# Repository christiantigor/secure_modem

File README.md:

secure_modem
============

Secure modem

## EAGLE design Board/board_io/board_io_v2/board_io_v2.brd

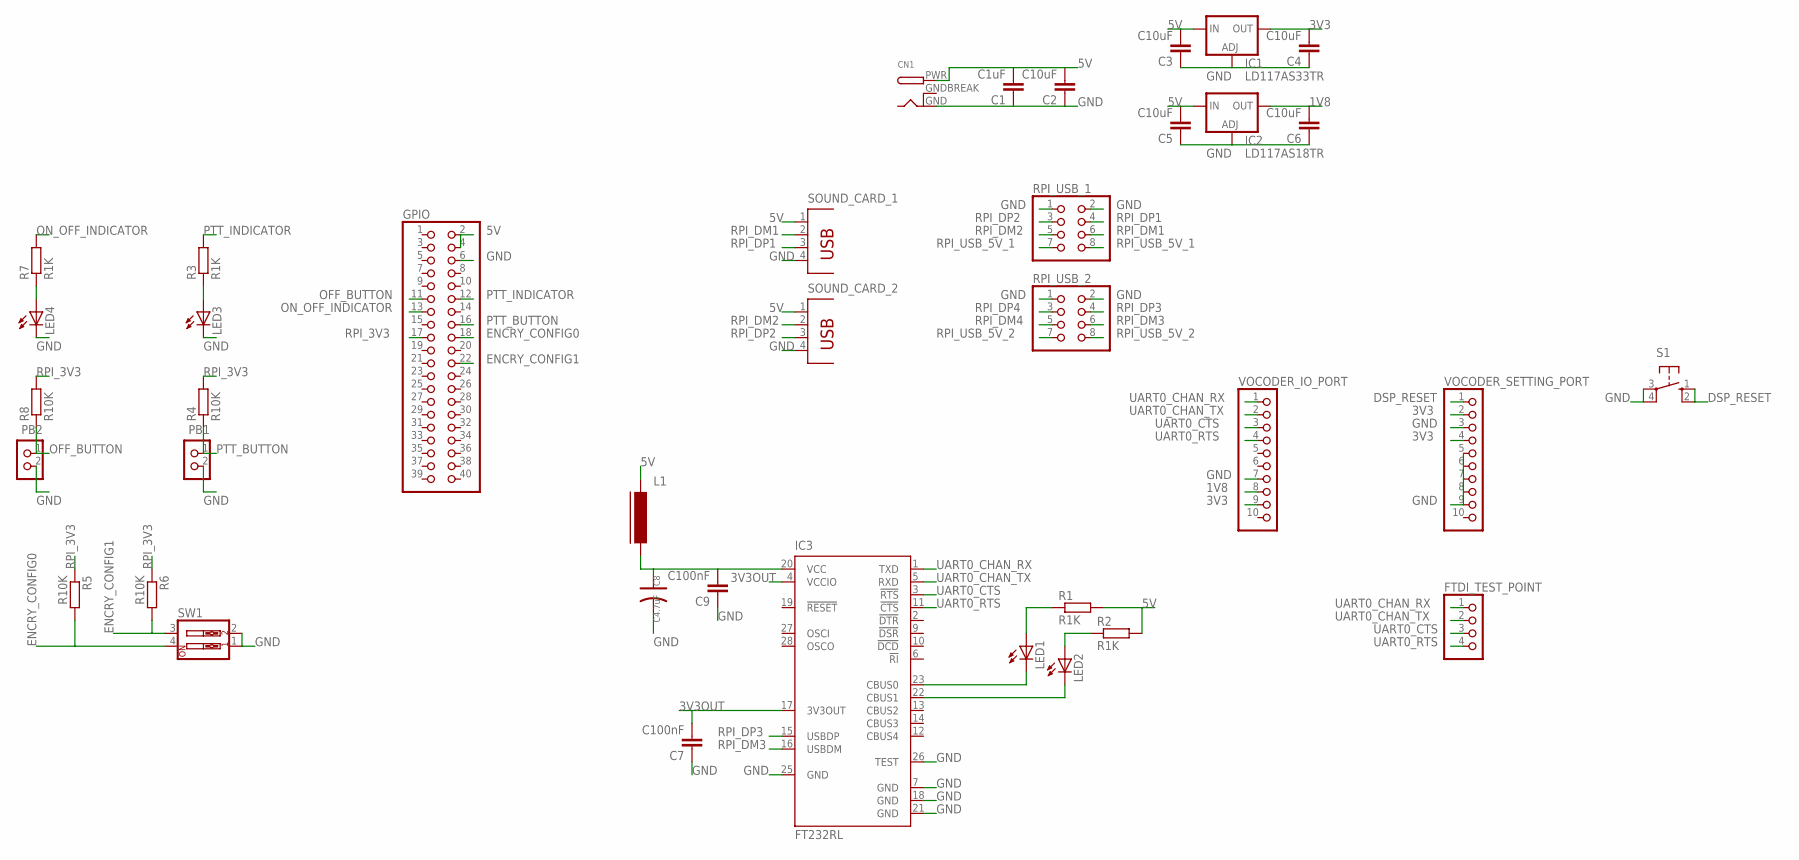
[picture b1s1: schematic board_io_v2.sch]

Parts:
C1: C1uF; C0805
C2, C3, C4, C5, C6: C10uF; C0805
C7, C9: C100nF; C0805
C8: C4.7uF; AVX-C
CN1: DCBARRELPTH; DCJACK_2MM_PTH
FTDI_TEST_POINT: PINHD-1X4; 1X04
GPIO: PINHD-2X20; 2X20
IC1: LD117AS33TR; SOT223
IC2: LD117AS18TR; SOT223
IC3: FT232RL; SSOP28
L1: FERRITE-0603; FB603
LED1, LED2, LED3, LED4: LEDCHIP-LED0805; CHIP-LED0805
PB1, PB2: CON_HEADER_1X02-PTH; M1X2
R1, R2, R3, R7: R1K; R0805
R4, R5, R6, R8: R10K; R0805
RPI_USB_1, RPI_USB_2: PINHD-2X4; 2X04
S1: 10-XX; B3F-10XX
SOUND_CARD_1, SOUND_CARD_2: PN87520
SW1: SW_DIP-2; DIPSWITCH-02
VOCODER_IO_PORT: PINHD-1X10; 1X10
VOCODER_SETTING_PORT: PINHD-1X10; 1X10

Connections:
1V8: C6.2, IC2.4 (OUT), VOCODER_IO_PORT.8
3V3: C4.2, IC1.4 (OUT), VOCODER_IO_PORT.9, VOCODER_SETTING_PORT.2, VOCODER_SETTING_PORT.4
3V3OUT: C7.2, IC3.4 (VCCIO), IC3.17 (3V3OUT)
5V: C1.2, C2.2, C3.2, C5.2, CN1.PWR, GPIO.2, GPIO.4, IC1.3 (IN), IC2.3 (IN), L1.1, R1.2, R2.2, SOUND_CARD_1.1, SOUND_CARD_2.1
DSP_RESET: S1.1 (S), S1.2 (S1), VOCODER_SETTING_PORT.1
ENCRY_CONFIG0: GPIO.18, R5.2, SW1.4
ENCRY_CONFIG1: GPIO.22, R6.2, SW1.3
GND: C1.1, C2.1, C3.1, C4.1, C5.1, C6.1, C7.1, C8.- (2), C9.1, CN1.GND, GPIO.6, IC1.1 (ADJ), IC2.1 (ADJ), IC3.7 (GND), IC3.18 (GND), IC3.21 (GND), IC3.25 (GND), IC3.26 (TEST), LED3.C, LED4.C, PB1.2, PB2.2, RPI_USB_1.1, RPI_USB_1.2, RPI_USB_2.1, RPI_USB_2.2, S1.3, S1.4 (P1), SOUND_CARD_1.4, SOUND_CARD_2.4, SW1.1, SW1.2, VOCODER_IO_PORT.7, VOCODER_SETTING_PORT.3, VOCODER_SETTING_PORT.5, VOCODER_SETTING_PORT.6, VOCODER_SETTING_PORT.7, VOCODER_SETTING_PORT.8, VOCODER_SETTING_PORT.9
GNDBREAK: CN1.GNDBREAK
unnamed: C8.+ (1), C9.2, IC3.20 (VCC), L1.2
unnamed: IC3.22 (CBUS1), LED2.C
unnamed: IC3.23 (CBUS0), LED1.C
unnamed: LED2.A, R2.1
unnamed: LED1.A, R1.1
unnamed: LED4.A, R7.1
unnamed: LED3.A, R3.1
OFF_BUTTON: GPIO.11, PB2.1, R8.1
ON_OFF_INDICATOR: GPIO.13, R7.2
PTT_BUTTON: GPIO.16, PB1.1, R4.1
PTT_INDICATOR: GPIO.12, R3.2
RPI_3V3: GPIO.17, R4.2, R5.1, R6.1, R8.2
RPI_DM1: RPI_USB_1.6, SOUND_CARD_1.2
RPI_DM2: RPI_USB_1.5, SOUND_CARD_2.2
RPI_DM3: IC3.16 (USBDM), RPI_USB_2.6
RPI_DM4: RPI_USB_2.5
RPI_DP1: RPI_USB_1.4, SOUND_CARD_1.3
RPI_DP2: RPI_USB_1.3, SOUND_CARD_2.3
RPI_DP3: IC3.15 (USBDP), RPI_USB_2.4
RPI_DP4: RPI_USB_2.3
RPI_USB_5V_1: RPI_USB_1.7, RPI_USB_1.8
RPI_USB_5V_2: RPI_USB_2.7, RPI_USB_2.8
UART0_CHAN_RX: FTDI_TEST_POINT.1, IC3.1 (TXD), VOCODER_IO_PORT.1
UART0_CHAN_TX: FTDI_TEST_POINT.2, IC3.5 (RXD), VOCODER_IO_PORT.2
UART0_CTS: FTDI_TEST_POINT.3, IC3.3 (!RTS), VOCODER_IO_PORT.3
UART0_RTS: FTDI_TEST_POINT.4, IC3.11 (!CTS), VOCODER_IO_PORT.4

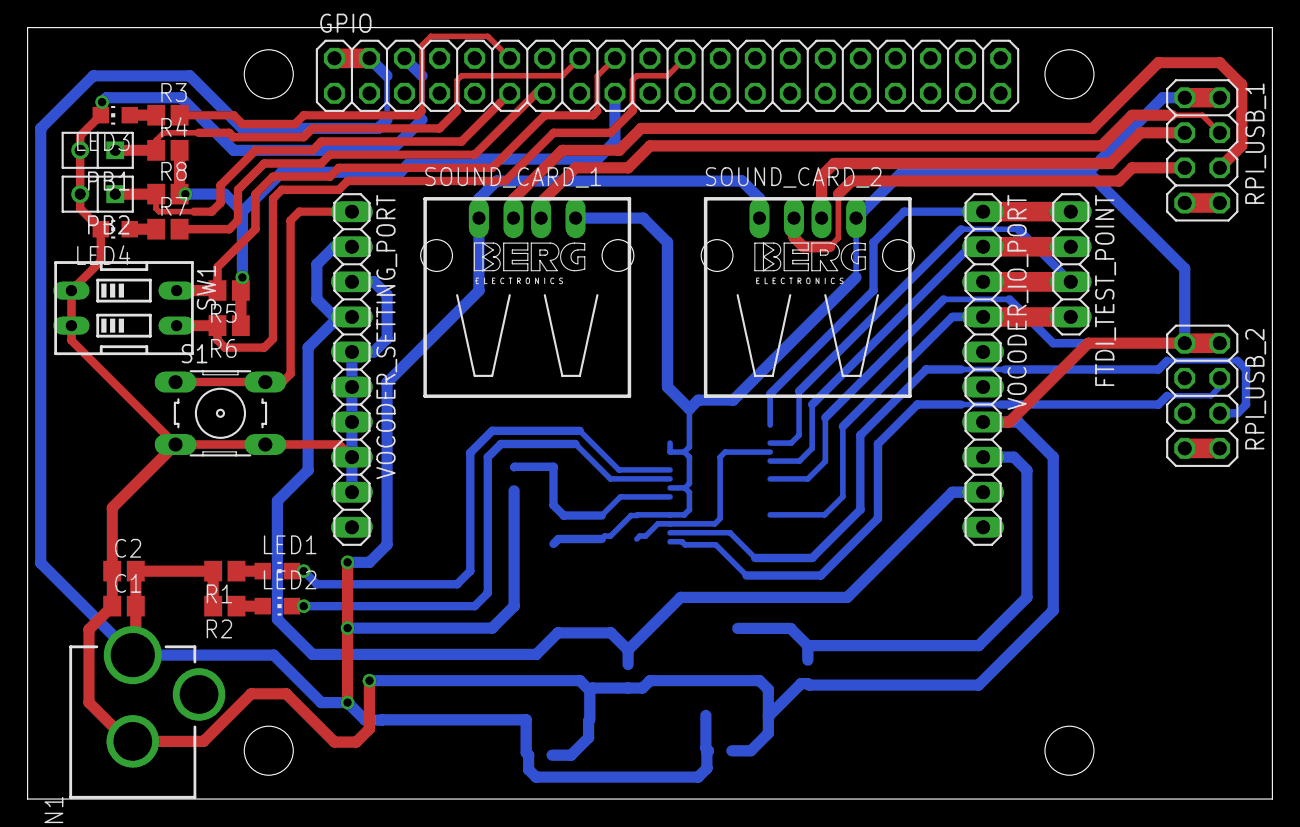
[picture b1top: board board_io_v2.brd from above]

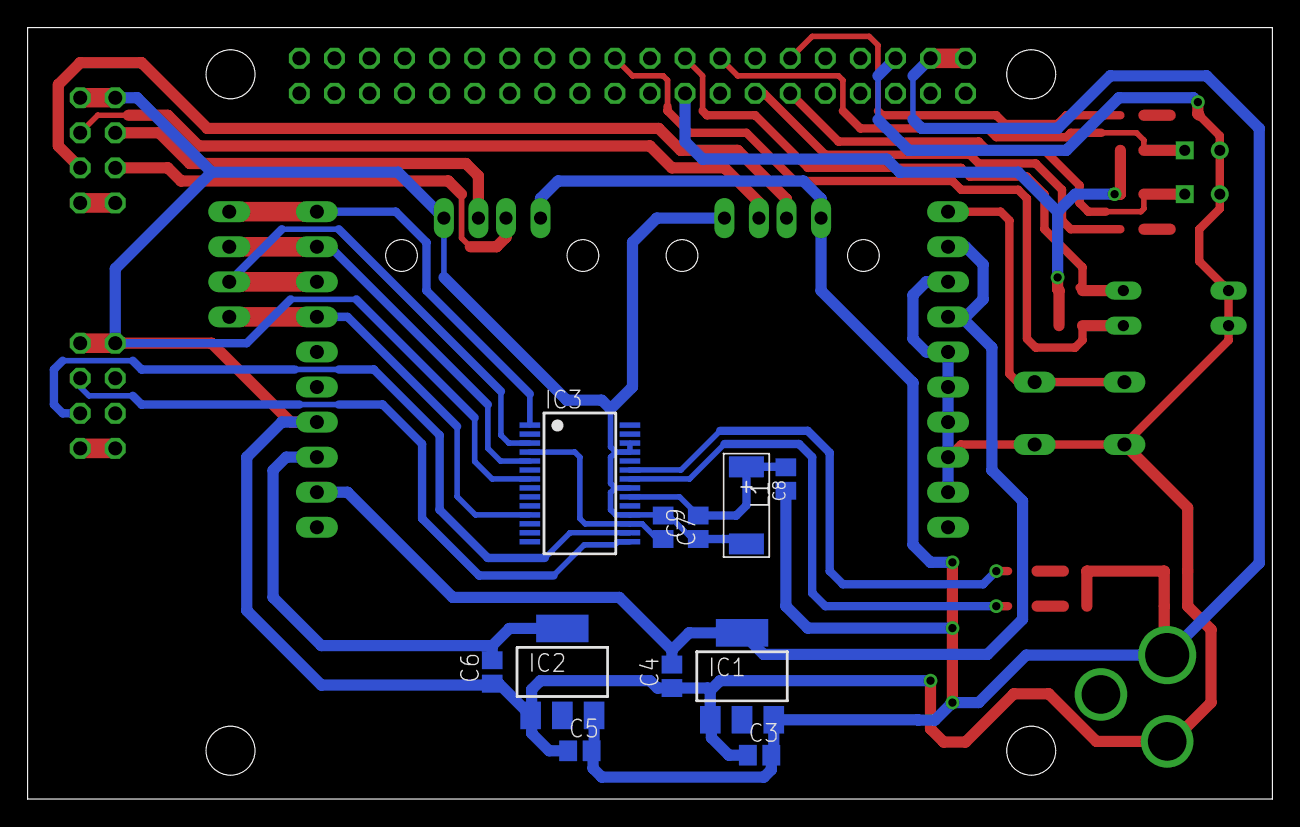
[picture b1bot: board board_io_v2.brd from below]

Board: 2 copper layers, 90.2 x 55.9 mm, 38 parts (11 on the bottom side), 32 nets.

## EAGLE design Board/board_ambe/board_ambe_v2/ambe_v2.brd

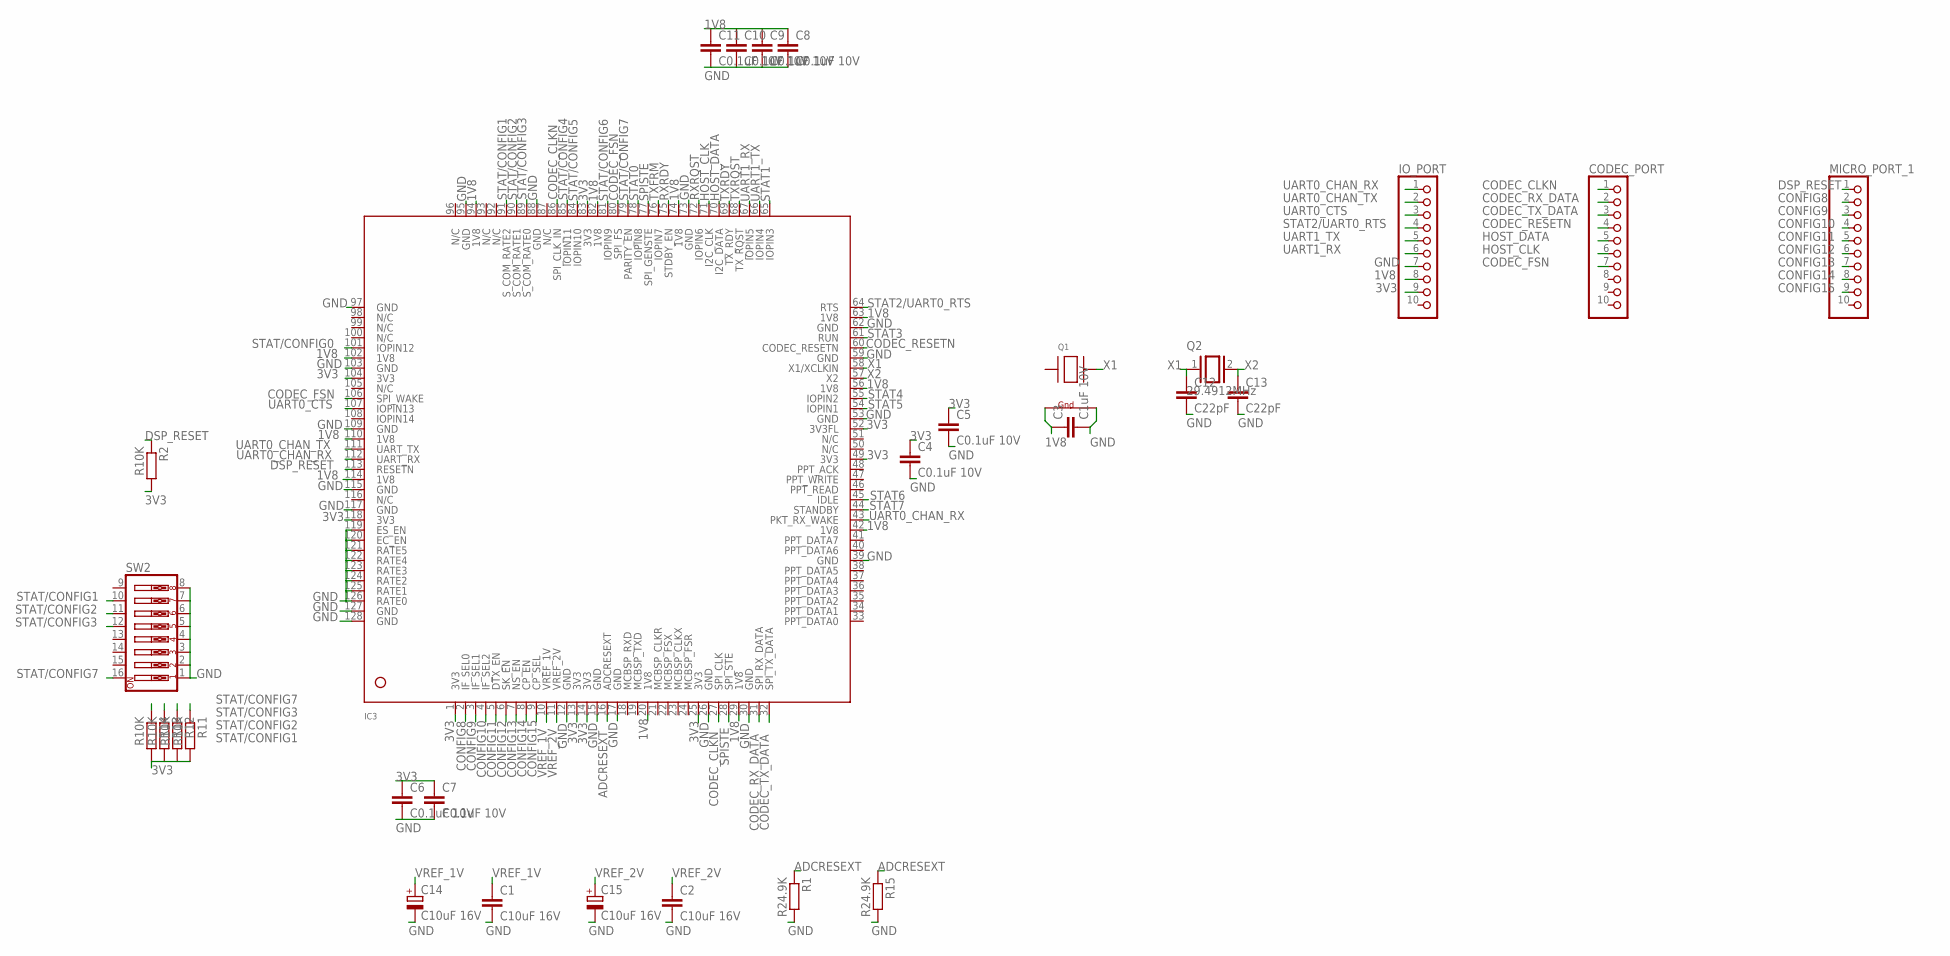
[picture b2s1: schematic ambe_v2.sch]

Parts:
C1, C2: C10uF 16V; C0805
C3: C1uF 10V; C0805
C4, C5, C6, C7, C8, C9, C10, C11: C0.1uF 10V; C0805
C12, C13: C22pF; C025-024X044
C14, C15: C10uF 16V; E2-4
CODEC_PORT: PINHD-1X10; 1X10
IC3: AMBE-3000LQFP-128; LQFP-128
IO_PORT: PINHD-1X10; 1X10
MICRO_PORT_1: PINHD-1X10; 1X10
Q1: XTAL-4-3225; NX3225
Q2: 29.4912MHz; QS
R1: R24.9K; R0805
R2, R11, R12, R13, R14: R10K; R0805
R15: R24.9K; 0207/2V
SW2: SW_DIP-8; DIPSWITCH-08

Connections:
1V8: C3.1, C8.1, C9.1, C10.1, C11.1, IC3.20 (1V8), IC3.29 (1V8), IC3.42 (1V8), IC3.56 (1V8), IC3.63 (1V8), IC3.74 (1V8), IC3.82 (1V8), IC3.94 (1V8), IC3.102 (1V8), IC3.110 (1V8), IC3.114 (1V8), IO_PORT.8, Q1.4 (G1)
3V3: C4.1, C5.1, C6.1, C7.1, IC3.1 (3V3), IC3.13 (3V3), IC3.14 (3V3), IC3.25 (3V3), IC3.49 (3V3), IC3.52 (3V3FL), IC3.83 (3V3), IC3.104 (3V3), IC3.118 (3V3), IO_PORT.9, R2.2, R11.2, R12.2, R13.2, R14.2
ADCRESEXT: IC3.16 (ADCRESEXT), R1.1, R15.1
CODEC_CLKN: CODEC_PORT.1, IC3.27 (SPI_CLK), IC3.86 (SPI_CLK_IN)
CODEC_FSN: CODEC_PORT.7, IC3.80 (SPI_FS), IC3.106 (SPI_WAKE)
CODEC_RESETN: CODEC_PORT.4, IC3.60 (CODEC_RESETN)
CODEC_RX_DATA: CODEC_PORT.2, IC3.31 (SPI_RX_DATA)
CODEC_TX_DATA: CODEC_PORT.3, IC3.32 (SPI_TX_DATA)
CONFIG8: IC3.2 (IF_SEL0), MICRO_PORT_1.2
CONFIG9: IC3.3 (IF_SEL1), MICRO_PORT_1.3
CONFIG10: IC3.4 (IF_SEL2), MICRO_PORT_1.4
CONFIG11: IC3.5 (DTX_EN), MICRO_PORT_1.5
CONFIG12: IC3.6 (SK_EN), MICRO_PORT_1.6
CONFIG13: IC3.7 (NS_EN), MICRO_PORT_1.7
CONFIG14: IC3.8 (CP_EN), MICRO_PORT_1.8
CONFIG15: IC3.9 (CP_SEL), MICRO_PORT_1.9
DSP_RESET: IC3.113 (RESETN), MICRO_PORT_1.1, R2.1
GND: C1.2, C2.2, C3.2, C4.2, C5.2, C6.2, C7.2, C8.2, C9.2, C10.2, C11.2, C12.2, C13.2, C14.-, C15.-, IC3.12 (GND), IC3.15 (GND), IC3.17 (GND), IC3.26 (GND), IC3.30 (GND), IC3.39 (GND), IC3.53 (GND), IC3.59 (GND), IC3.62 (GND), IC3.73 (GND), IC3.88 (GND), IC3.95 (GND), IC3.97 (GND), IC3.103 (GND), IC3.109 (GND), IC3.115 (GND), IC3.117 (GND), IC3.119 (ES_EN), IC3.120 (EC_EN), IC3.121 (RATE5), IC3.122 (RATE4), IC3.123 (RATE3), IC3.124 (RATE2), IC3.125 (RATE1), IC3.126 (RATE0), IC3.127 (GND), IC3.128 (GND), IO_PORT.7, Q1.2 (G2), R1.2, R15.2, SW2.1, SW2.2, SW2.3, SW2.4, SW2.5, SW2.6, SW2.7, SW2.8
HOST_CLK: CODEC_PORT.6, IC3.71 (I2C_CLK)
HOST_DATA: CODEC_PORT.5, IC3.70 (I2C_DATA)
RXRDY: IC3.75 (STDBY_EN)
RXRQST: IC3.72 (IOPIN6)
SPISTE: IC3.28 (SPI_STE), IC3.77 (SPI_GENSTE)
STAT0: IC3.78 (IOPIN8)
STAT1: IC3.65 (IOPIN3)
STAT2/UART0_RTS: IC3.64 (RTS), IO_PORT.4
STAT3: IC3.61 (RUN)
STAT4: IC3.55 (IOPIN2)
STAT5: IC3.54 (IOPIN1)
STAT6: IC3.45 (IDLE)
STAT7: IC3.44 (STANDBY)
STAT/CONFIG0: IC3.101 (IOPIN12)
STAT/CONFIG1: IC3.91 (S_COM_RATE2), R14.1, SW2.10
STAT/CONFIG2: IC3.90 (S_COM_RATE1), R13.1, SW2.11
STAT/CONFIG3: IC3.89 (S_COM_RATE0), R12.1, SW2.12
STAT/CONFIG4: IC3.85 (IOPIN11)
STAT/CONFIG5: IC3.84 (IOPIN10)
STAT/CONFIG6: IC3.81 (IOPIN9)
STAT/CONFIG7: IC3.79 (PARITY_EN), R11.1, SW2.16
TXFRM: IC3.76 (IOPIN7)
TXRDY: IC3.69 (TX_RDY)
TXRQST: IC3.68 (TX_RQST)
UART0_CHAN_RX: IC3.43 (PKT_RX_WAKE), IC3.112 (UART_RX), IO_PORT.1
UART0_CHAN_TX: IC3.111 (UART_TX), IO_PORT.2
UART0_CTS: IC3.107 (IOPIN13), IO_PORT.3
UART1_RX: IC3.67 (IOPIN5), IO_PORT.6
UART1_TX: IC3.66 (IOPIN4), IO_PORT.5
VREF_1V: C1.1, C14.+, IC3.10 (VREF_1V)
VREF_2V: C2.1, C15.+, IC3.11 (VREF_2V)
X1: C12.1, IC3.58 (X1/XCLKIN), Q1.3 (X2), Q2.1
X2: C13.1, IC3.57 (X2), Q2.2

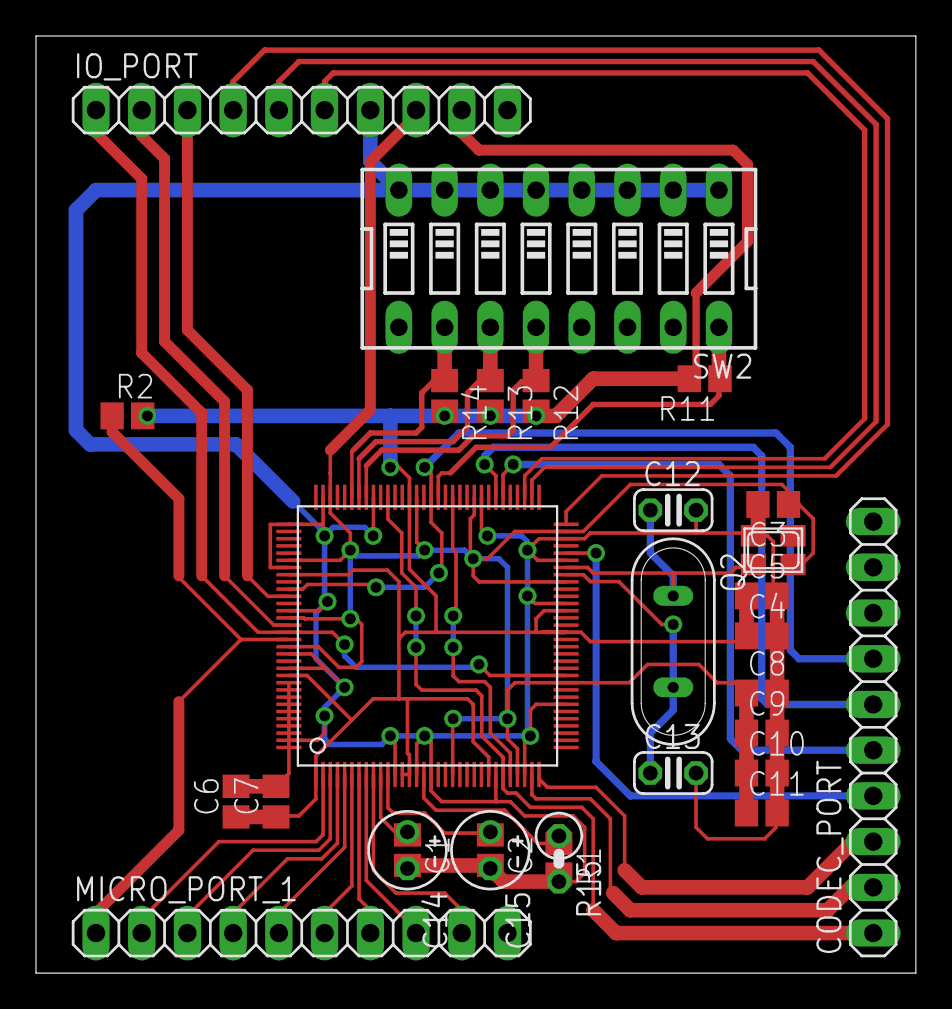
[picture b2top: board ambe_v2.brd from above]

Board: 2 copper layers, 48.9 x 52.1 mm, 29 parts (0 on the bottom side), 35 nets.

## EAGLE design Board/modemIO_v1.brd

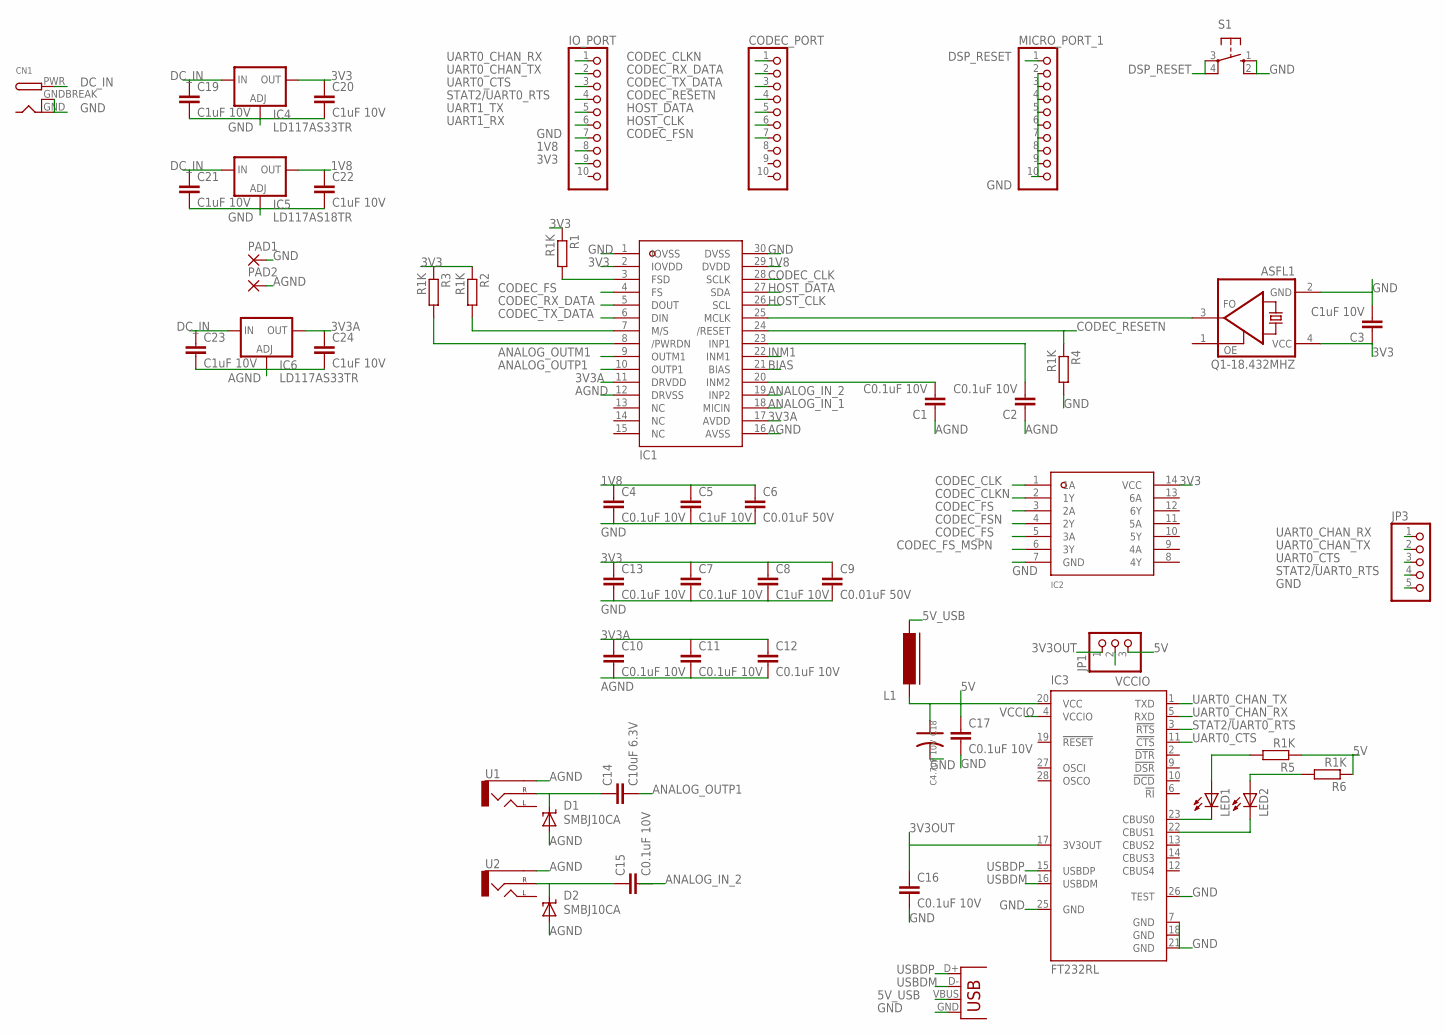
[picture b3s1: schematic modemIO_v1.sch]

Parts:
C1, C2, C4, C7, C10, C11, C12, C13, C15, C16, C17: C0.1uF 10V; C0805
C3, C5, C8, C19, C20, C21, C22, C23, C24: C1uF 10V; C0805
C6, C9: C0.01uF 50V; C0805
C14: C10uF 6.3V; C0805
C18: C4.7uF 10V; AVX-C
CN1: DCBARRELPTH; DCJACK_2MM_PTH
CODEC_PORT: PINHD-1X10; 1X10
D1, D2: SMBJ10CA; SMBJ
IC1: TLV320AIC14R-PDSO-G30; R-PDSO-G30
IC2: SN74LVC04ADRR-PDSO-G14; R-PDSO-G14
IC3: FT232RL; SSOP28
IC4, IC6: LD117AS33TR; SOT223
IC5: LD117AS18TR; SOT223
IO_PORT: PINHD-1X10; 1X10
JP1: PINHD-1X3; 1X03
JP2: USBSMD; USB-MINIB
JP3: PINHD-1X5; 1X05
L1: FERRITE-0603; FB603
LED1, LED2: LEDCHIP-LED0805; CHIP-LED0805
MICRO_PORT_1: PINHD-1X10; 1X10
PAD1, PAD2: SMD2; SMD1,27-2,54
Q1-18.432MHZ: ASFL1; ASF
R1, R2, R3, R4, R5, R6: R1K; R0805
S1: 10-XX; B3F-10XX
U1, U2: AUDIO-JACKSMD2; AUDIO-JACK-3.5MM-SMD

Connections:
1V8: C4.1, C5.1, C6.1, C22.1, IC1.29 (DVDD), IC5.4 (OUT), IO_PORT.8
3V3: C3.1, C7.1, C8.1, C9.1, C13.1, C20.1, IC1.2 (IOVDD), IC2.14 (VCC), IC4.4 (OUT), IO_PORT.9, Q1-18.432MHZ.4 (VCC), R1.1, R2.1, R3.1
3V3A: C10.1, C11.1, C12.1, C24.1, IC1.11 (DRVDD), IC1.17 (AVDD), IC6.4 (OUT)
3V3OUT: C16.1, IC3.17 (3V3OUT), JP1.1
5V: C17.1, C18.+ (1), IC3.20 (VCC), JP1.3, L1.1, R5.1, R6.1
5V_USB: JP2.VBUS, L1.2
AGND: C1.1, C2.1, C10.2, C11.2, C12.2, C23.2, C24.2, D1.A, D2.A, IC1.12 (DRVSS), IC1.16 (AVSS), IC6.1 (ADJ), PAD2.1, U1.SLEEVE, U2.SLEEVE
ANALOG_IN_1: IC1.18 (MICIN)
ANALOG_IN_2: C15.2, IC1.19 (INP2)
ANALOG_OUTM1: IC1.9 (OUTM1)
ANALOG_OUTP1: C14.2, IC1.10 (OUTP1)
BIAS: IC1.21 (BIAS)
CODEC_CLK: IC1.28 (SCLK), IC2.1 (1A)
CODEC_CLKN: CODEC_PORT.1, IC2.2 (1Y)
CODEC_FS: IC1.4 (FS), IC2.3 (2A), IC2.5 (3A)
CODEC_FSN: CODEC_PORT.7, IC2.4 (2Y)
CODEC_FS_MSPN: IC2.6 (3Y)
CODEC_RESETN: CODEC_PORT.4, IC1.24 (/RESET), R4.1
CODEC_RX_DATA: CODEC_PORT.2, IC1.5 (DOUT)
CODEC_TX_DATA: CODEC_PORT.3, IC1.6 (DIN)
DC_IN: C19.1, C21.1, C23.1, CN1.PWR, IC4.3 (IN), IC5.3 (IN), IC6.3 (IN)
DSP_RESET: MICRO_PORT_1.1, S1.3, S1.4 (P1)
GND: C3.2, C4.2, C5.2, C6.2, C7.2, C8.2, C9.2, C13.2, C16.2, C17.2, C18.- (2), C19.2, C20.2, C21.2, C22.2, CN1.GND, CN1.GNDBREAK, IC1.1 (IOVSS), IC1.30 (DVSS), IC2.7 (GND), IC3.7 (GND), IC3.18 (GND), IC3.21 (GND), IC3.25 (GND), IC3.26 (TEST), IC4.1 (ADJ), IC5.1 (ADJ), IO_PORT.7, JP2.GND, JP3.5, MICRO_PORT_1.2, MICRO_PORT_1.3, MICRO_PORT_1.4, MICRO_PORT_1.5, MICRO_PORT_1.6, MICRO_PORT_1.7, MICRO_PORT_1.8, MICRO_PORT_1.9, MICRO_PORT_1.10, PAD1.1, Q1-18.432MHZ.2 (GND), R4.2, S1.1 (S), S1.2 (S1)
HOST_CLK: CODEC_PORT.6, IC1.26 (SCL)
HOST_DATA: CODEC_PORT.5, IC1.27 (SDA)
INM1: IC1.22 (INM1)
unnamed: C14.1, D1.C, U1.RING (RIGHT)
unnamed: IC3.23 (CBUS0), LED1.C
unnamed: IC1.3 (FSD), R1.2
unnamed: IC3.22 (CBUS1), LED2.C
unnamed: C15.1, D2.C, U2.RING (RIGHT)
unnamed: LED1.A, R5.2
unnamed: IC1.7 (M/S), R2.2
unnamed: IC1.8 (/PWRDN), R3.2
unnamed: LED2.A, R6.2
unnamed: C1.2, IC1.20 (INM2)
unnamed: C2.2, IC1.23 (INP1)
unnamed: IC1.25 (MCLK), Q1-18.432MHZ.3 (FO)
STAT2/UART0_RTS: IC3.3 (!RTS), IO_PORT.4, JP3.4
UART0_CHAN_RX: IC3.5 (RXD), IO_PORT.1, JP3.1
UART0_CHAN_TX: IC3.1 (TXD), IO_PORT.2, JP3.2
UART0_CTS: IC3.11 (!CTS), IO_PORT.3, JP3.3
UART1_RX: IO_PORT.6
UART1_TX: IO_PORT.5
USBDM: IC3.16 (USBDM), JP2.D-
USBDP: IC3.15 (USBDP), JP2.D+
VCCIO: IC3.4 (VCCIO), JP1.2

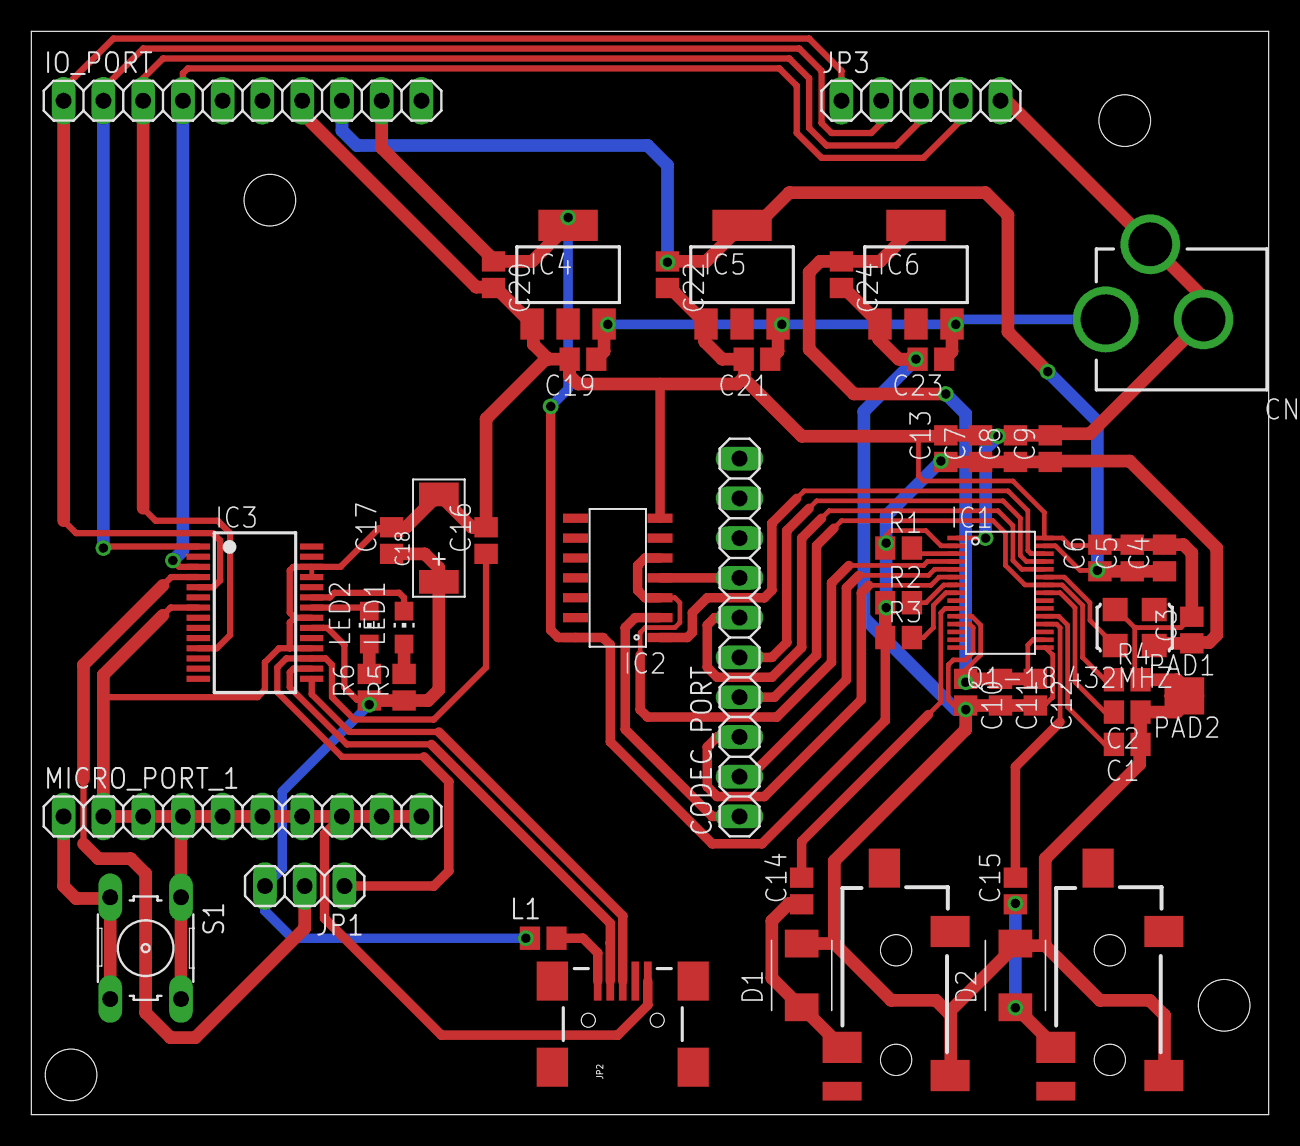
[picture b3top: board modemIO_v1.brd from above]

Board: 2 copper layers, 79.0 x 69.2 mm, 54 parts (0 on the bottom side), 40 nets.

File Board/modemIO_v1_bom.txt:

Partlist exported from C:/Users/tritronik/Documents/GitHub/secure_modem/Board/modemIO_v1.sch at 27/08/2014 12:49:14

Assembly variant: 

Qty Value                  Device                 Parts                                            
1                          10-XX                  S1                                               
2                          AUDIO-JACKSMD2         U1, U2                                           
1                          DCBARRELPTH            CN1                                              
1                          FERRITE-0603           L1                                               
2                          LEDCHIP-LED0805        LED1, LED2                                       
1                          PINHD-1X3              JP1                                              
1                          PINHD-1X5              JP3                                              
3                          PINHD-1X10             CODEC_PORT, IO_PORT, MICRO_PORT_1                
2                          SMD2                   PAD1, PAD2                                       
1   ASFL1                  ASFL1                  Q1-18.432MHZ                                     
11  C0.1uF 10V             C-EUC0805              C1, C2, C4, C7, C10, C11, C12, C13, C15, C16, C17
2   C0.01uF 50V            C-EUC0805              C6, C9                                           
9   C1uF 10V               C-EUC0805              C3, C5, C8, C19, C20, C21, C22, C23, C24         
1   C4.7uF 10V             C-POLAR-C              C18                                              
1   C10uF 6.3V             C-EUC0805              C14                                              
1   FT232RL                FT232RL                IC3                                              
1   LD117AS18TR            LD117AS18TR            IC5                                              
2   LD117AS33TR            LD117AS33TR            IC4, IC6                                         
6   R1K                    R-EU_R0805             R1, R2, R3, R4, R5, R6                           
2   SMBJ10CA               SUPPRESSOR-SMBJ        D1, D2                                           
1   SN74LVC04ADRR-PDSO-G14 SN74LVC04ADRR-PDSO-G14 IC2                                              
1   TLV320AIC14R-PDSO-G30  TLV320AIC14R-PDSO-G30  IC1                                              
1   USBSMD                 USBSMD                 JP2

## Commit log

2014-07-22 :space_invader: Added .gitattributes & .gitignore files
2014-07-25 Second commit
2014-07-25 Add DV3000DS and custom lib
2014-08-04 Progress on routing board
2014-08-05 Finish routing ambe board
2014-08-05 Create modemIO
2014-08-05 Add custom lib for codec and inverter
2014-08-07 + pull up to AMBE's Reset & progress in ModemIO brd
2014-08-11 Finish routing modemIO board
2014-08-27 Change pad size of AMBE IC
2014-08-29 Reposition vias on board
2014-09-09 Move custom lib to board dir
2014-09-09 Add AMBE sample
2014-09-09 Move custom lib
2014-09-18 add notes
2014-10-27 Init presentation files
2014-11-07 add presentation
2014-11-07 add interfacing ppt, change ppt template
2014-11-11 add py code encod encry n mod, explore FEC
2014-11-11 add encryption code demo, not using FEC
2014-11-11 add audio codec ppt, and codec matlab example
2014-11-14 add presentation day one and two
2014-11-17 update demo compression with matlab
2014-11-17 update audio_c2 for ubuntu
2015-01-21 add presentation, driver, and notes of hdkcom
2015-01-22 rearrange hdkcom notes
2015-01-23 add play_manual.py code
2015-01-26 not able to enter uart codec mode from custom app
2015-01-26 enter uart codec mode by set boot up to a3kdirect
2015-01-28 manual recording from usb
2015-01-28 play_manual_p1 can be played repeatedly w/o reset
2015-01-28 success to record and play manual from p1
2015-02-02 init packet mode
2015-02-02 encode_manual_usb can be played
2015-02-02 encode_manual_p1
2015-02-05 add encode and decode code for rpi
2015-02-10 add ambe and io board
2015-02-11 update io board and add interface code
2015-02-12 add zfec and reed solomon
2015-02-17 add notes on how to play and record correctly
2015-02-20 debug record and demod with piping
2015-02-20 correct record with piping
2015-02-23 start to integrate app
2015-02-23 integrate encoding
2015-02-23 integrate encryption and modulation
2015-02-24 update mainapp
2015-02-25 separate main app (send & rec) and test a3k code
2015-02-25 test en&dec (handle a3k encoding size, 18 byte)
    Test encrypt and decrypt. Handle a3k ending size (18 bytes)
2015-02-25 create and test fec module
2015-02-25 update and test transmit module
2015-02-25 update fec and kripto modules
2015-02-25 fair ex of send n recv w/o encryption
2015-02-25 send n recv w encryption
2015-03-11 start edit reedsolo for unfec, add trivium
2015-03-13 use reedsolosource.py in mainapp
2015-05-05 add timeline doc for phase 2

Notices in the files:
parts and their libraries:
SparkFun-Electromechanical: Licensing: CC v3.0 Share-Alike You are welcome to use this library for commercial purposes.
